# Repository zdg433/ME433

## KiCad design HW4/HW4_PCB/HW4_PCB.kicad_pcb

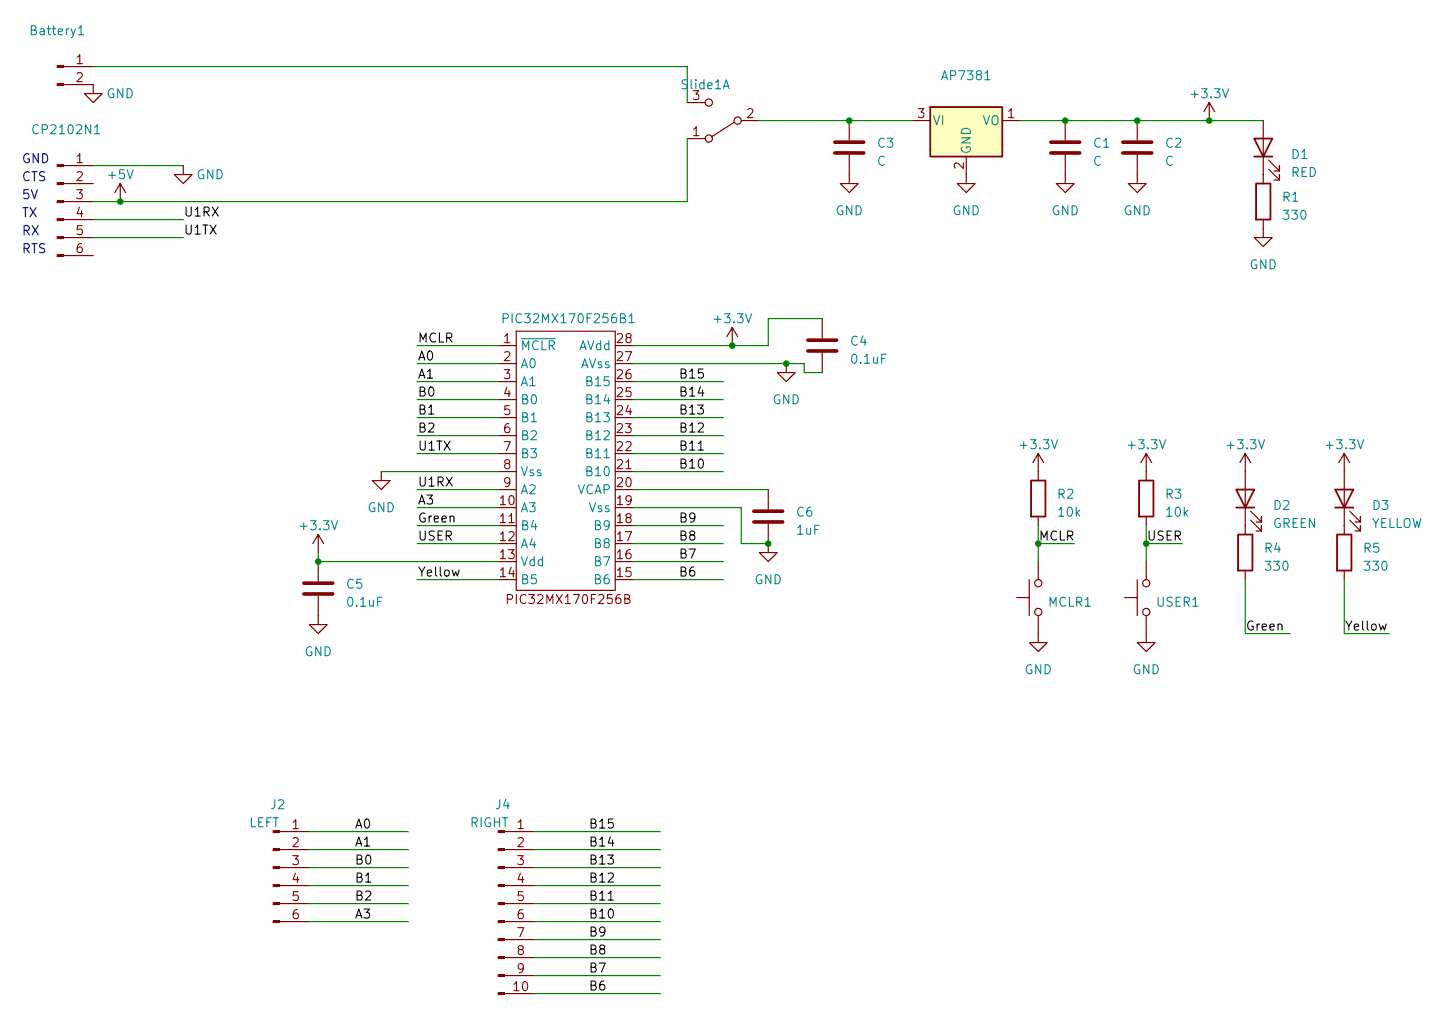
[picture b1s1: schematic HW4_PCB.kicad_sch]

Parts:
AP7381: TO-92L_Inline
Battery1: PinSocket_1x02_P2.54mm_Vertical
C1, C2, C3: C; C_Disc_D5.1mm_W3.2mm_P5.00mm
C4, C5: 0.1uF; C_Disc_D3.4mm_W2.1mm_P2.50mm
C6: 1uF; C_Disc_D5.1mm_W3.2mm_P5.00mm
CP2102N1: PinSocket_1x06_P2.54mm_Vertical
D1: RED; LED_D3.0mm
D2: GREEN; LED_D3.0mm
D3: YELLOW; LED_D3.0mm
J2: LEFT; PinSocket_1x06_P2.54mm_Vertical
J4: RIGHT; PinSocket_1x10_P2.54mm_Vertical
MCLR1: pb
PIC32MX170F256B1: DIP-28_W7.62mm_Socket
R1, R4, R5: 330; R_Axial_DIN0207_L6.3mm_D2.5mm_P7.62mm_Horizontal
R2, R3: 10k; R_Axial_DIN0207_L6.3mm_D2.5mm_P7.62mm_Horizontal
Slide1: slidesw2
USER1: pb

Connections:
+3.3V: AP7381.1 (VO), C1.1, C2.1, C4.1, C5.1, D1.2 (A), D2.2 (A), D3.2 (A), PIC32MX170F256B1.13 (Vdd), PIC32MX170F256B1.28 (AVdd), R2.1, R3.1
+5V: CP2102N1.3, Slide1.1 (A)
/A0: J2.1, PIC32MX170F256B1.2 (A0)
/A1: J2.2, PIC32MX170F256B1.3 (A1)
/A3: J2.6, PIC32MX170F256B1.10 (A3)
/B0: J2.3, PIC32MX170F256B1.4 (B0)
/B1: J2.4, PIC32MX170F256B1.5 (B1)
/B2: J2.5, PIC32MX170F256B1.6 (B2)
/B6: J4.10, PIC32MX170F256B1.15 (B6)
/B7: J4.9, PIC32MX170F256B1.16 (B7)
/B8: J4.8, PIC32MX170F256B1.17 (B8)
/B9: J4.7, PIC32MX170F256B1.18 (B9)
/B10: J4.6, PIC32MX170F256B1.21 (B10)
/B11: J4.5, PIC32MX170F256B1.22 (B11)
/B12: J4.4, PIC32MX170F256B1.23 (B12)
/B13: J4.3, PIC32MX170F256B1.24 (B13)
/B14: J4.2, PIC32MX170F256B1.25 (B14)
/B15: J4.1, PIC32MX170F256B1.26 (B15)
/Green: PIC32MX170F256B1.11 (B4), R4.2
/MCLR: MCLR1.2, PIC32MX170F256B1.1 (~MCLR), R2.2
/U1RX: CP2102N1.4, PIC32MX170F256B1.9 (A2)
/U1TX: CP2102N1.5, PIC32MX170F256B1.7 (B3)
/USER: PIC32MX170F256B1.12 (A4), R3.2, USER1.2
/Yellow: PIC32MX170F256B1.14 (B5), R5.2
GND: AP7381.2 (GND), Battery1.2, C1.2, C2.2, C3.2, C4.2, C5.2, C6.2, CP2102N1.1, MCLR1.1, PIC32MX170F256B1.8 (Vss), PIC32MX170F256B1.19 (Vss), PIC32MX170F256B1.27 (AVss), R1.2, USER1.1
unnamed: AP7381.3 (VI), C3.1, Slide1.2 (B)
unnamed: Battery1.1, Slide1.3 (C)
unnamed: D1.1 (K), R1.1
unnamed: D2.1 (K), R4.1
unnamed: D3.1 (K), R5.1
unnamed: C6.1, PIC32MX170F256B1.20 (VCAP)

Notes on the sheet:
CTS
RTS
GND

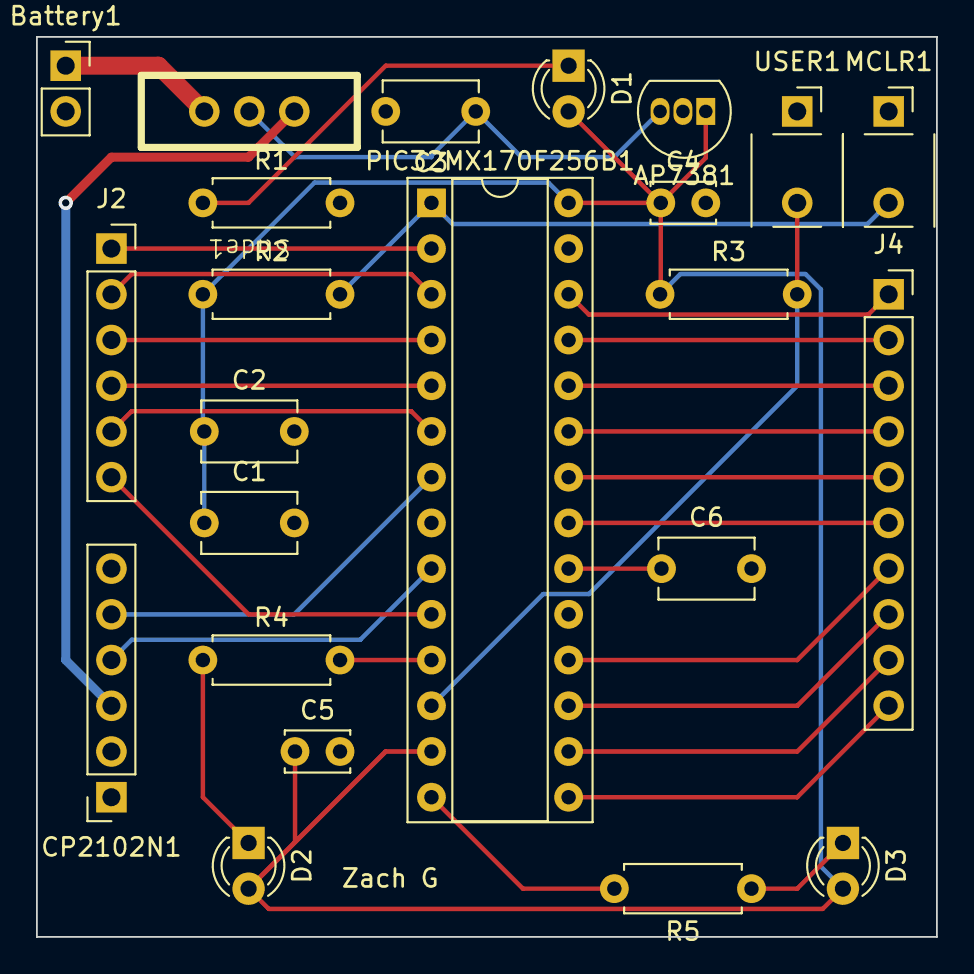
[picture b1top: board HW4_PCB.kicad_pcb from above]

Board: 2 copper layers, 50.0 x 50.0 mm, 23 parts (0 on the bottom side), 31 nets.

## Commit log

2023-04-04 HW2 stuff
2023-04-10 some stuff
2023-04-18 HW4 stuff
2023-04-25 HW5 stuff
2023-04-27 HW6 Stuff
2023-04-28 HW7 stuff
2023-04-28 HW3 Stuff
2023-05-04 HW8 stuff
2023-05-18 HW9 stuff
2023-05-28 HW10
2023-05-29 HW11
    I wasn't sure how to plot a 2 axis graph with circuit python so I took a screen shot (of a paused screen recording) of the plotting tool with the 3 peeks of the FFT present
2023-06-08 HW 15 stuff
2023-06-08 HW14 Stuff
